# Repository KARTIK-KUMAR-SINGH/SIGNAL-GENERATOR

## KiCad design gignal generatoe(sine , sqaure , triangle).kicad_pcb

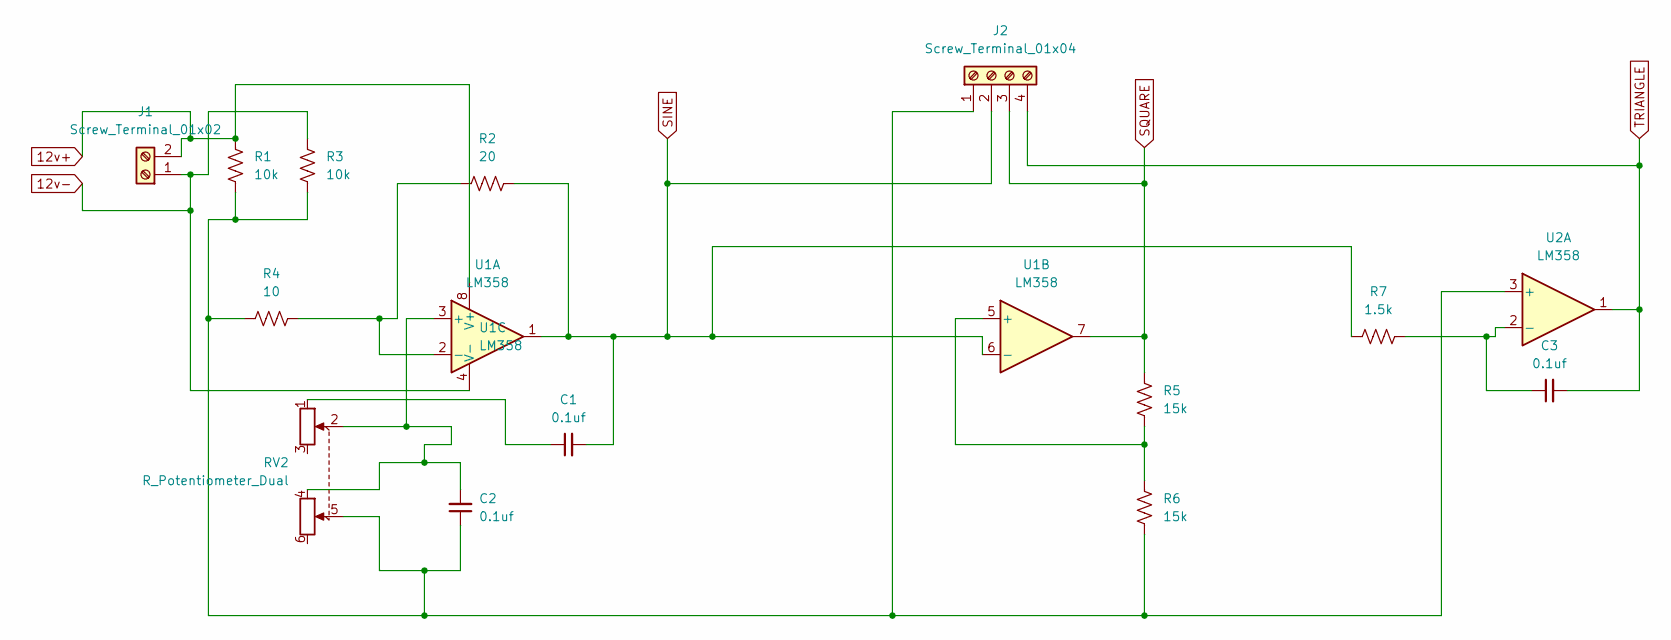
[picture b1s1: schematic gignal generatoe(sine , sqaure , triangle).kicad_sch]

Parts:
C1, C2, C3: 0.1uf; C_Disc_D7.5mm_W2.5mm_P5.00mm
J1: Screw_Terminal_01x02; TerminalBlock_MaiXu_MX126-5.0-02P_1x02_P5.00mm
J2: Screw_Terminal_01x04; TerminalBlock_MaiXu_MX126-5.0-04P_1x04_P5.00mm
R1, R3: 10k; R_Axial_DIN0309_L9.0mm_D3.2mm_P15.24mm_Horizontal
R2: 20; R_Axial_DIN0309_L9.0mm_D3.2mm_P15.24mm_Horizontal
R4: 10; R_Axial_DIN0309_L9.0mm_D3.2mm_P15.24mm_Horizontal
R5, R6: 15k; R_Axial_DIN0309_L9.0mm_D3.2mm_P15.24mm_Horizontal
R7: 1.5k; R_Axial_DIN0309_L9.0mm_D3.2mm_P15.24mm_Horizontal
RV2: R_Potentiometer_Dual; Potentiometer_Alps_RK163_Dual_Horizontal
U1, U2: LM358; CERDIP-8_W7.62mm_SideBrazed_Socket

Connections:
12v+: J1.2, R1.2, U1.8 (V+)
12v-: J1.1, R3.1, U1.4 (V-)
unnamed: C1.1, RV2.1
unnamed: C2.1, J2.1, R1.1, R3.2, R4.1, R6.2, RV2.5, U2.3 (+)
unnamed: C2.2, RV2.2, RV2.4, U1.3 (+)
unnamed: R2.1, R4.2, U1.2 (-)
unnamed: R5.2, R6.1, U1.5 (+)
unnamed: C3.1, R7.2, U2.2 (-)
SINE: C1.2, J2.2, R2.2, R7.1, U1.1, U1.6 (-)
SQUARE: J2.3, R5.1, U1.7
TRIANGLE: C3.2, J2.4, U2.1

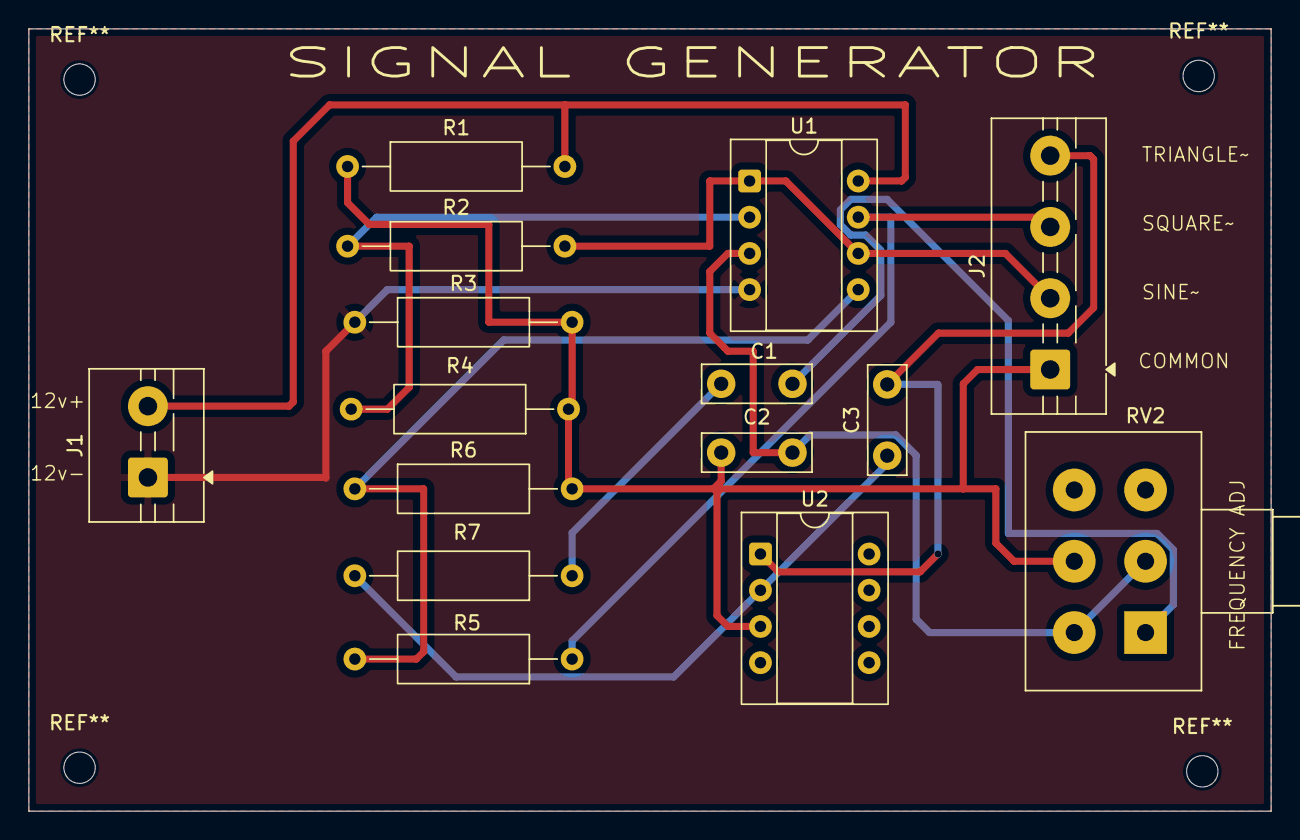
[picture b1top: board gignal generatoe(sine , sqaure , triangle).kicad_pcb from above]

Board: 2 copper layers, 87.1 x 54.9 mm, 15 parts (0 on the bottom side), 11 nets.

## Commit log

2026-02-21 Initial commit: LM358 Signal Generator project with PCB and Gerber files
2026-02-21 name change of the jpeg files
